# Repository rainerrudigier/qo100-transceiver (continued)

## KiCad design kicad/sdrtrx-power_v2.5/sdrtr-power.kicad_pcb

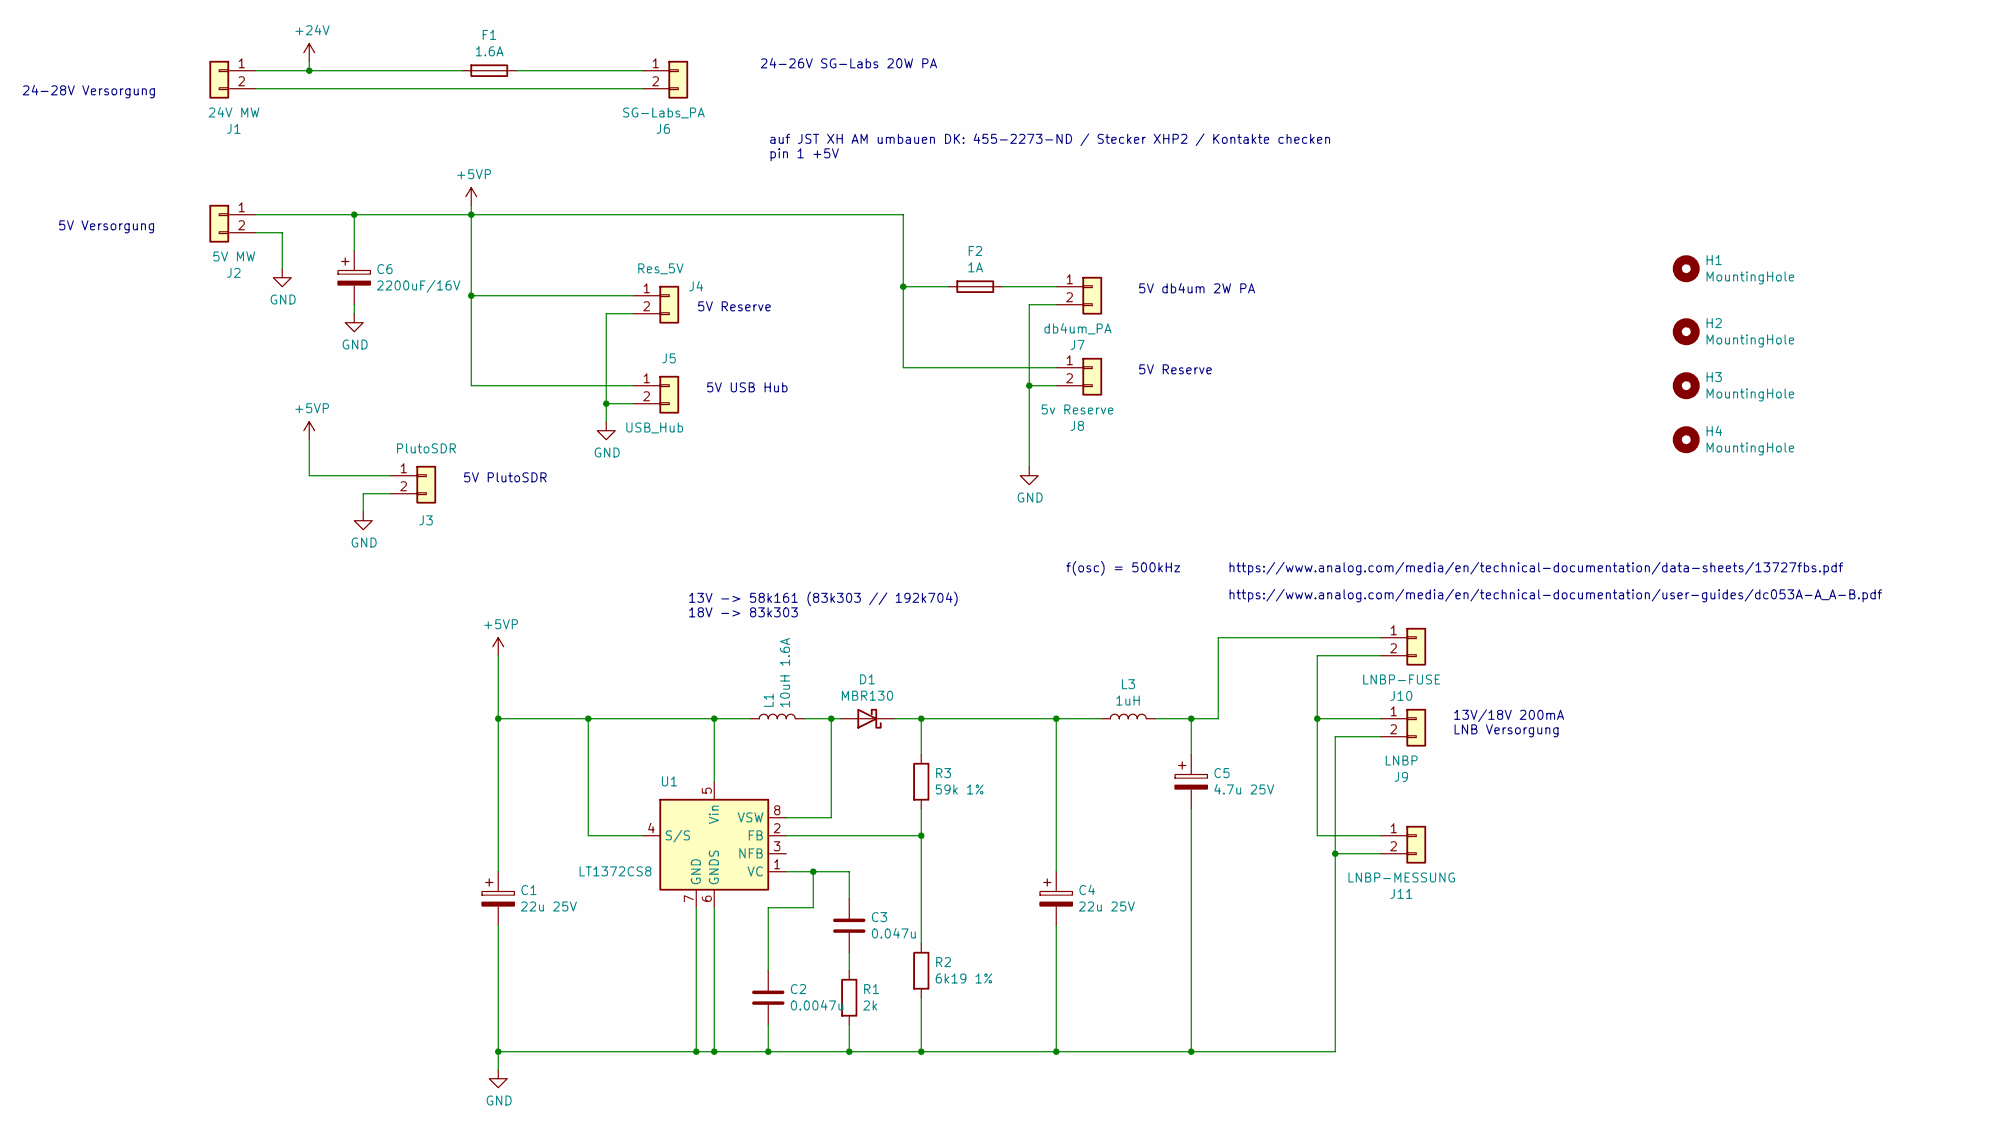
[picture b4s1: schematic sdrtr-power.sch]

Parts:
C1, C4: 22u 25V; CP_EIA-7343-30_AVX-N_Pad2.25x2.55mm_HandSolder; DigiKey 478-4106-1-ND
C2: 0.0047u; C_1206_3216Metric; DigiKey 478-10870-1-ND
C3: 0.047u; C_1206_3216Metric; DigiKey 478-3793-1-ND
C5: 4.7u 25V; CP_EIA-3528-15_AVX-H_Pad1.50x2.35mm_HandSolder; DigiKey 478-11105-1-ND
C6: 2200uF/16V; CP_Radial_D12.5mm_P5.00mm; Digikey 493-4884-1-ND
D1: MBR130; D_SOD-123; DigiKey MBR130T1GOSCT-ND
F1: 1.6A; Fuse_2920_7451Metric_Pad2.10x5.45mm_HandSolder; DigiKey F5965CT-ND
F2: 1A; Fuse_1210_3225Metric_Pad1.42x2.65mm_HandSolder; DigiKey F5964CT-ND
H1, H2, H3, H4: MountingHole; MountingHole_3.2mm_M3_Pad
J1: 24V MW; SolderWire-1sqmm_1x02_P5.4mm_D1.4mm_OD2.7mm
J2: 5V MW; SolderWire-1sqmm_1x02_P5.4mm_D1.4mm_OD2.7mm
J3: PlutoSDR; JST_XH_B2B-XH-AM_1x02_P2.50mm_Vertical; DigiKey 455-2273-ND
J4: Res_5V; JST_XH_B2B-XH-AM_1x02_P2.50mm_Vertical; DigiKey 455-2273-ND
J5: USB_Hub; JST_XH_B2B-XH-AM_1x02_P2.50mm_Vertical; DigiKey 455-2273-ND
J6: SG-Labs_PA; JST_XH_B2B-XH-AM_1x02_P2.50mm_Vertical; DigiKey 455-1704-ND
J7: db4um_PA; JST_XH_B2B-XH-AM_1x02_P2.50mm_Vertical; DigiKey 455-2273-ND
J8: 5v Reserve; JST_XH_B2B-XH-AM_1x02_P2.50mm_Vertical; DigiKey 455-2273-ND
J9: LNBP; Molex_PicoBlade_53047-0210_1x02_P1.25mm_Vertical; DigiKey WM1731-ND
J10: LNBP-FUSE; Molex_PicoBlade_53047-0210_1x02_P1.25mm_Vertical; DigiKey WM1731-ND
J11: LNBP-MESSUNG; Molex_PicoBlade_53047-0210_1x02_P1.25mm_Vertical; DigiKey WM1731-ND
L1: 10uH 1.6A; L_7.3x7.3_H3.5; DigiKey 308-2127-1-ND
L3: 1uH; L_1008_2520Metric; DigiKey 308-2608-1-ND
R1: 2k; R_0805_2012Metric; DigiKey 541-4134-1-ND
R2: 6k19 1%; R_0805_2012Metric; DigiKey 541-6.19KCCT-ND
R3: 59k 1%; R_0805_2012Metric; DigiKey 541-59.0KCCT-ND
U1: LT1372CS8; SOIC-8_3.9x4.9mm_P1.27mm; DigiKey LT1372CS8#TRPBFCT-ND

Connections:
+5VP: C1.1, C6.1, F2.2, J2.1, J3.1, J4.1, J5.1, J8.1, L1.1, U1.4 (S/S), U1.5 (Vin)
+24V: F1.2, J1.1
GND: C1.2, C2.2, C4.2, C5.2, C6.2, J2.2, J3.2, J4.2, J5.2, J7.2, J8.2, J9.2, J11.2, R1.2, R2.2, U1.6 (GNDS), U1.7 (GND)
unnamed: C2.1, C3.1, U1.1 (VC)
unnamed: C3.2, R1.1
unnamed: C4.1, D1.1 (K), L3.1, R3.1
unnamed: C5.1, J10.1, L3.2
unnamed: D1.2 (A), L1.2, U1.8 (VSW)
unnamed: F1.1, J6.1
unnamed: F2.1, J7.1
unnamed: J1.2, J6.2
unnamed: J9.1, J10.2, J11.1
unnamed: R2.1, R3.2, U1.2 (FB)

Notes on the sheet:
13V/18V 200mA LNB Versorgung
5V Versorgung
5V PlutoSDR
5V Reserve
5V USB Hub
5V db4um 2W PA
24-26V SG-Labs 20W PA
24-28V Versorgung
f(osc) = 500kHz
https://www.analog.com/media/en/technical-documentation/data-sheets/13727fbs.pdf
13V -> 58k161 (83k303 // 192k704) 18V -> 83k303
https://www.analog.com/media/en/technical-documentation/user-guides/dc053A-A_A-B.pdf
auf JST XH AM umbauen DK: 455-2273-ND / Stecker XHP2 / Kontakte checken pin 1 +5V

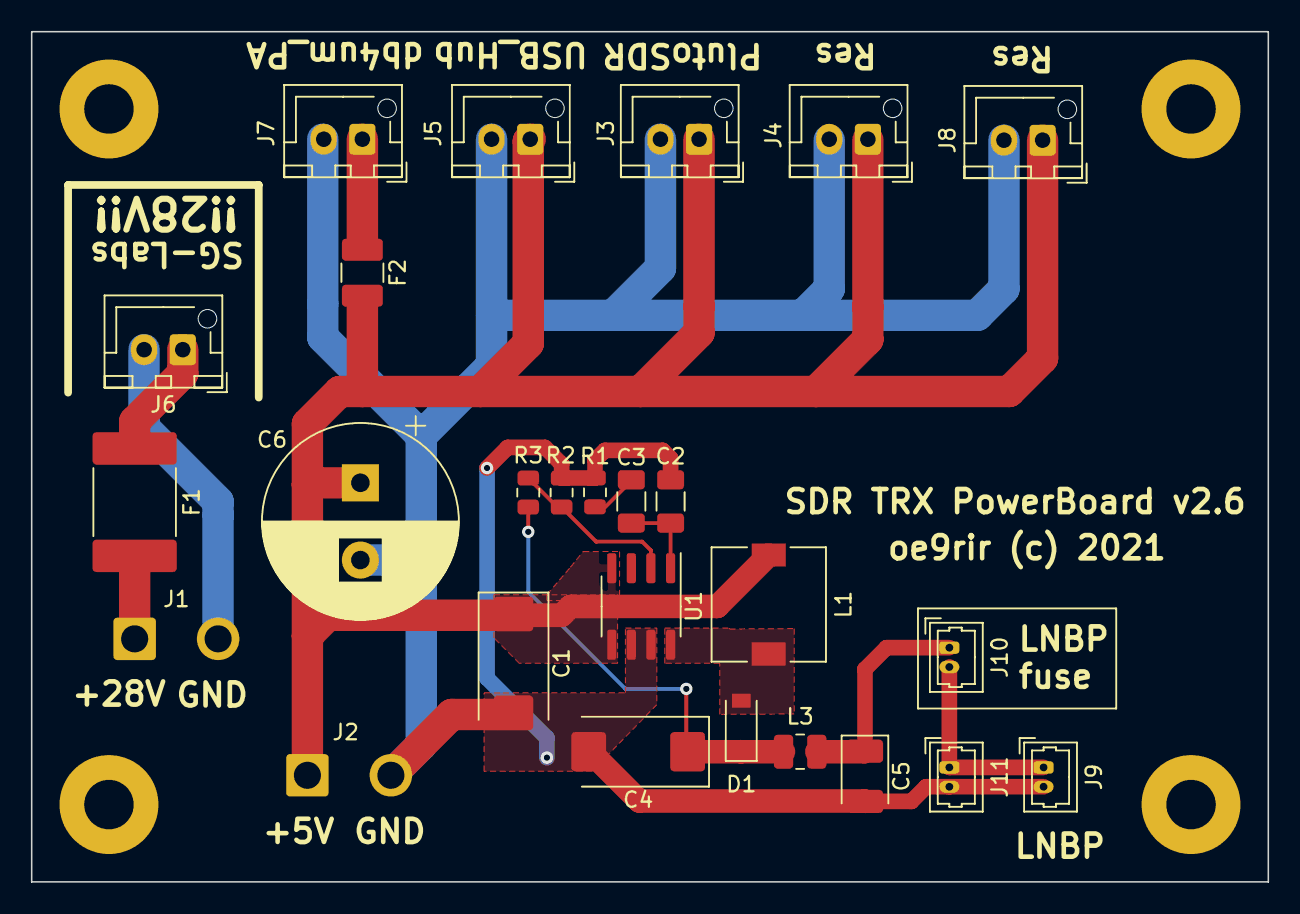
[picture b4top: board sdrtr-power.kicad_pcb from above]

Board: 2 copper layers, 80.0 x 55.0 mm, 30 parts (0 on the bottom side), 13 nets.

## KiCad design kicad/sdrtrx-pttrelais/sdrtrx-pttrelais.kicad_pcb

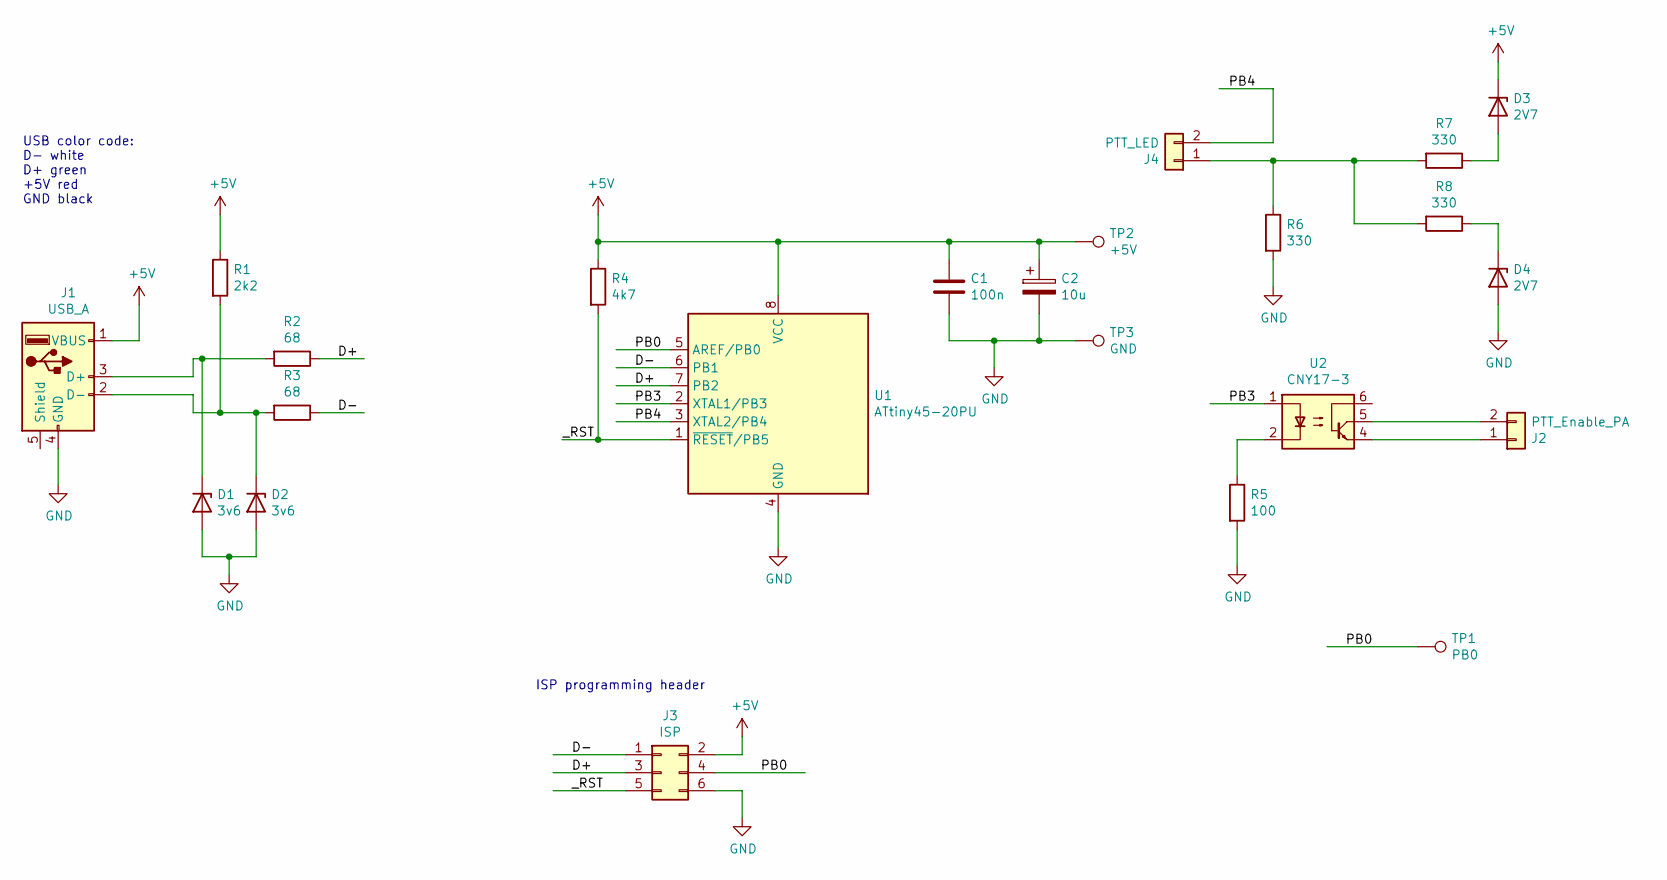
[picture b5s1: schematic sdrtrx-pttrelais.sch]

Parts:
C1: 100n; C_0805_2012Metric
C2: 10u; CP_Elec_4x5.8; Digikey 10-EEE-FN1A100RCT-ND
D1, D2: 3v6; D_SOD-123; Digikey MMSZ5227BT1GOSCT-ND
D3, D4: 2V7; D_SOD-123
J1: USB_A; USB_A_CNCTech_1001-011-01101_Horizontal; Digikey 1175-1008-ND
J2: PTT_Enable_PA; Molex_PicoBlade_53047-0210_1x02_P1.25mm_Vertical
J3: ISP; PinHeader_2x03_P1.27mm_Vertical
J4: PTT_LED; Molex_PicoBlade_53047-0210_1x02_P1.25mm_Vertical
R1: 2k2; R_0805_2012Metric
R2, R3: 68; R_0805_2012Metric
R4: 4k7; R_0805_2012Metric
R5: 100; R_0805_2012Metric
R6, R7, R8: 330; R_0805_2012Metric
TP1: PB0; TestPoint_Pad_D1.5mm
TP2: +5V; TestPoint_Pad_D1.5mm
TP3: GND; TestPoint_Pad_D1.5mm
U1: ATtiny45-20PU; SOIC-8_5.275x5.275mm_P1.27mm; Digikey ATTINY45-20SURCT-ND
U2: CNY17-3; CNY17_10x8.60mm_P2.54mm; Digikey CNY17-3X017TCT-ND

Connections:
+5V: C1.1, C2.1, D3.1 (K), J1.1 (VBUS), J3.2, R1.1, R4.1, TP2.1, U1.8 (VCC)
/D+: J3.3, R2.1, U1.7 (PB2)
/D-: J3.1, R3.1, U1.6 (PB1)
/PB0: J3.4, TP1.1, U1.5 (AREF/PB0)
/PB3: U1.2 (XTAL1/PB3), U2.1
/PB4: J4.2, U1.3 (XTAL2/PB4)
/_RST: J3.5, R4.2, U1.1 (~RESET~/PB5)
GND: C1.2, C2.2, D1.2 (A), D2.2 (A), D4.2 (A), J1.4 (GND), J3.6, R5.2, R6.2, TP3.1, U1.4 (GND)
unnamed: D1.1 (K), J1.3 (D+), R2.2
unnamed: D2.1 (K), J1.2 (D-), R1.2, R3.2
unnamed: D3.2 (A), R7.1
unnamed: D4.1 (K), R8.1
unnamed: J2.1, U2.4
unnamed: J2.2, U2.5
unnamed: J4.1, R6.1, R7.2, R8.2
unnamed: R5.1, U2.2

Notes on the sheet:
USB color code: D- white D+ green +5V red GND black
ISP programming header

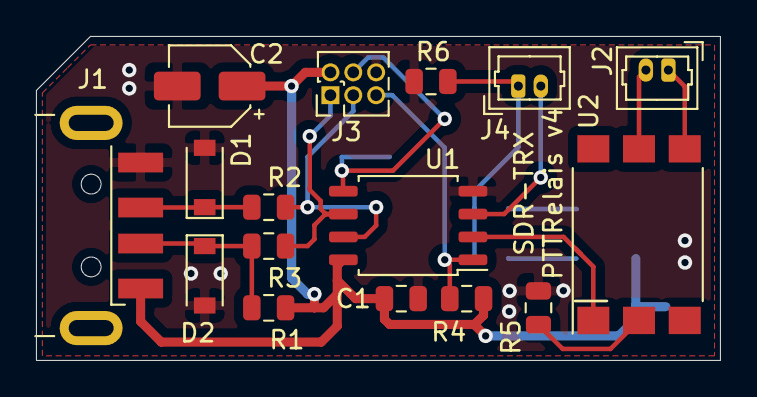
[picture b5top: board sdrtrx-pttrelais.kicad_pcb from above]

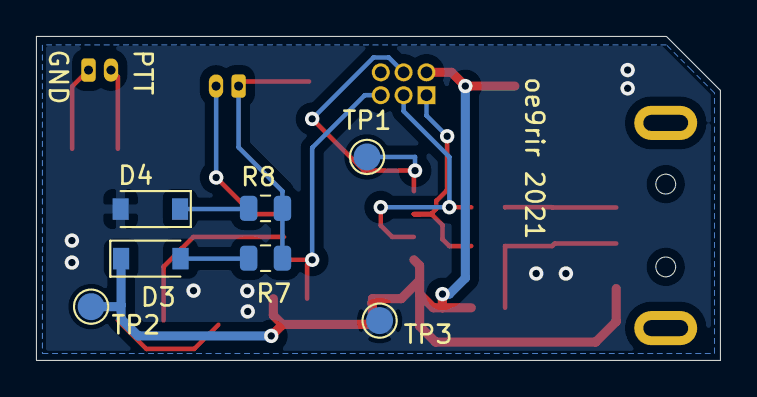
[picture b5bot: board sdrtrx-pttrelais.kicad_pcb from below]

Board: 2 copper layers, 38.0 x 18.0 mm, 23 parts (7 on the bottom side), 16 nets.

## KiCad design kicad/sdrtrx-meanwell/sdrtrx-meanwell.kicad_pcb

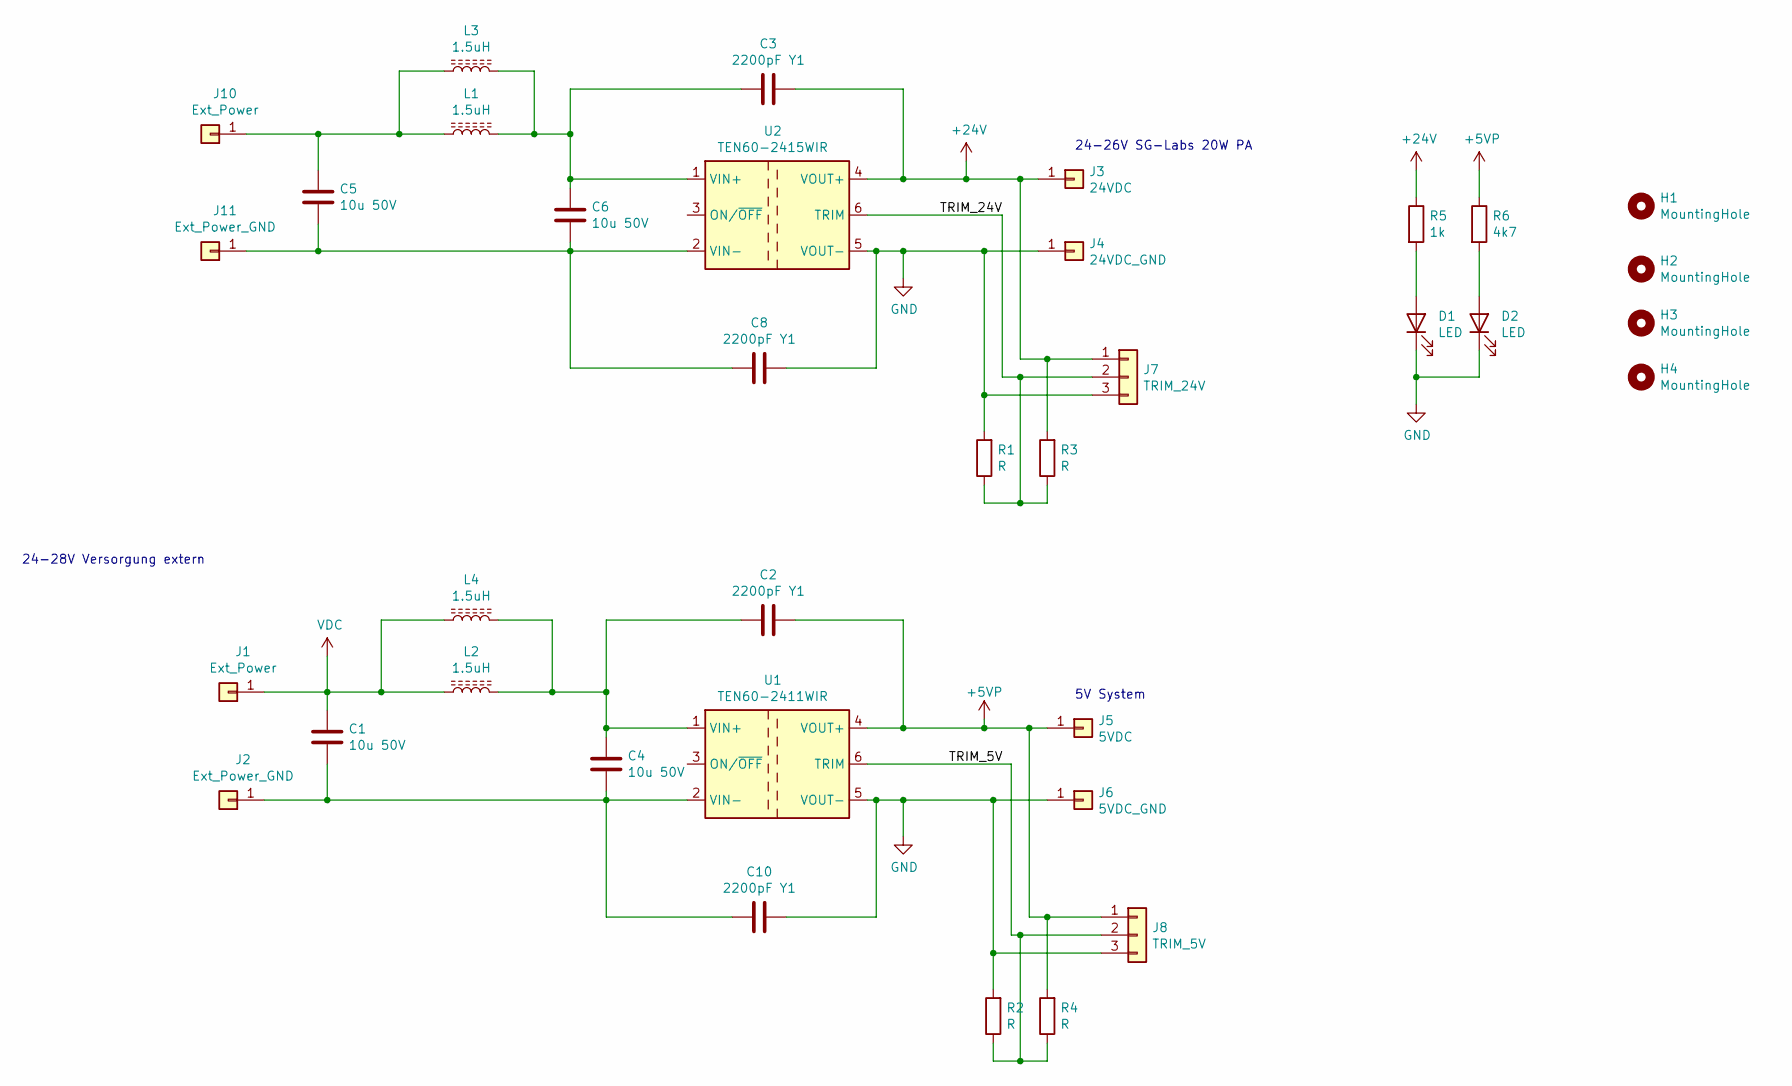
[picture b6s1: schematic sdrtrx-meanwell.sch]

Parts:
C1, C4, C5, C6: 10u 50V; C_1210_3225Metric_Pad1.42x2.65mm_HandSolder; DigiKey 399-C1210C106K5PAC7210CT-ND
C2, C3, C8, C10: 2200pF Y1; C_Disc_D11.0mm_W5.0mm_P10.00mm; DigiKey 490-16263-1-ND
D1, D2: LED; LED_0805_2012Metric
H1, H2, H3, H4: MountingHole; MountingHole_3.2mm_M3_Pad
J1, J10: Ext_Power; SolderWire-1sqmm_1x01_D1.4mm_OD2.7mm
J2, J11: Ext_Power_GND; SolderWire-1sqmm_1x01_D1.4mm_OD2.7mm
J3: 24VDC; SolderWire-1sqmm_1x01_D1.4mm_OD2.7mm
J4: 24VDC_GND; SolderWire-1sqmm_1x01_D1.4mm_OD2.7mm
J5: 5VDC; SolderWire-1sqmm_1x01_D1.4mm_OD2.7mm
J6: 5VDC_GND; SolderWire-1sqmm_1x01_D1.4mm_OD2.7mm
J7: TRIM_24V; Molex_PicoBlade_53398-0371_1x03-1MP_P1.25mm_Vertical; DigiKey WM7607CT-ND
J8: TRIM_5V; Molex_PicoBlade_53398-0371_1x03-1MP_P1.25mm_Vertical; DigiKey WM7607CT-ND
L1, L2: 1.5uH; L_Axial_L12.0mm_D5.0mm_P5.08mm_Vertical_Fastron_MISC
L3, L4: 1.5uH; L_Axial_L14.0mm_D4.0mm_P9.2mm_Horizontal_AML04A14-2R2M6R5-S1
R1, R2, R3, R4: R; R_0805_2012Metric_Pad1.15x1.40mm_HandSolder
R5: 1k; R_0805_2012Metric
R6: 4k7; R_0805_2012Metric
U1: TEN60-2411WIR; Converter_DCDC_TRACO_TEN60-xxxx_THT; DigiKey 1951-TEN60-2411WIR-ND
U2: TEN60-2415WIR; Converter_DCDC_TRACO_TEN60-xxxx_THT; DigiKey 1951-TEN60-2415WIR-ND

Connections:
+5VP: C2.2, J5.1, J8.1, R4.2, R6.1, U1.4 (VOUT+)
+24V: C3.1, J3.1, J7.1, R3.2, R5.1, U2.4 (VOUT+)
/TRIM_5V: J8.2, R2.1, R4.1, U1.6 (TRIM)
/TRIM_24V: J7.2, R1.1, R3.1, U2.6 (TRIM)
GND: C8.1, C10.1, D1.1 (K), D2.1 (K), J4.1, J6.1, J7.3, J8.3, R1.2, R2.2, U1.5 (VOUT-), U2.5 (VOUT-)
unnamed: C1.2, C4.2, C10.2, J2.1, U1.2 (VIN-)
unnamed: C2.1, C4.1, L2.2, L4.2, U1.1 (VIN+)
unnamed: C3.2, C6.1, L1.2, L3.2, U2.1 (VIN+)
unnamed: C5.1, J10.1, L1.1, L3.1
unnamed: C5.2, C6.2, C8.2, J11.1, U2.2 (VIN-)
unnamed: D1.2 (A), R5.2
unnamed: D2.2 (A), R6.2
VDC: C1.1, J1.1, L2.1, L4.1

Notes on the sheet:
5V System
24-26V SG-Labs 20W PA
24-28V Versorgung extern

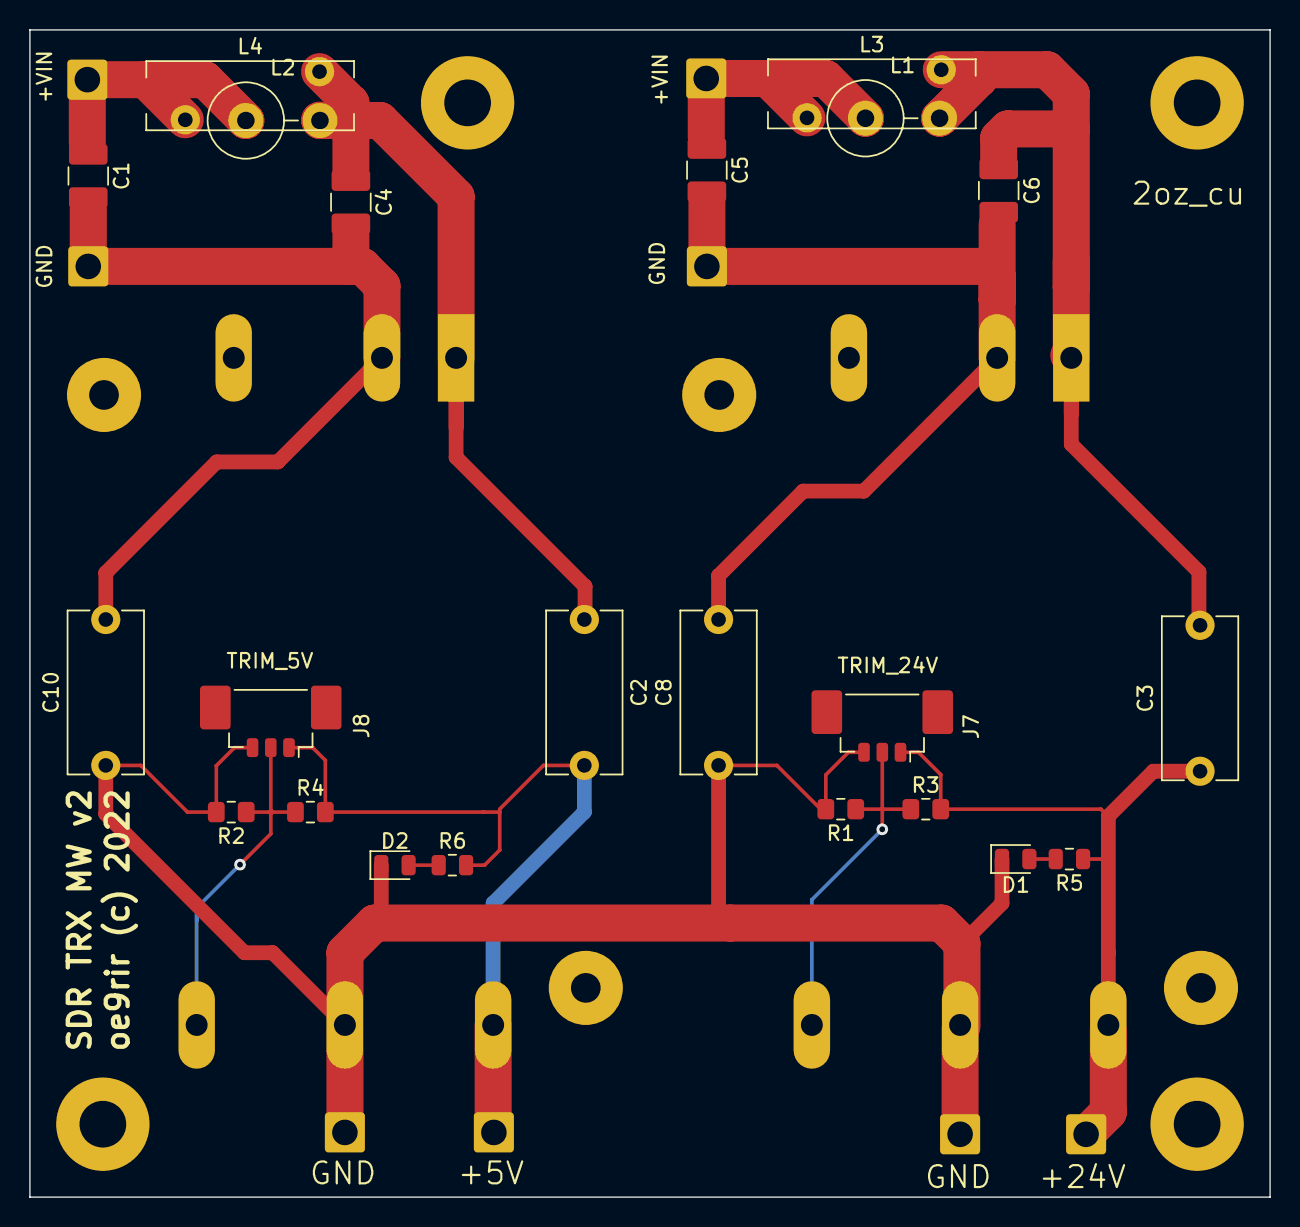
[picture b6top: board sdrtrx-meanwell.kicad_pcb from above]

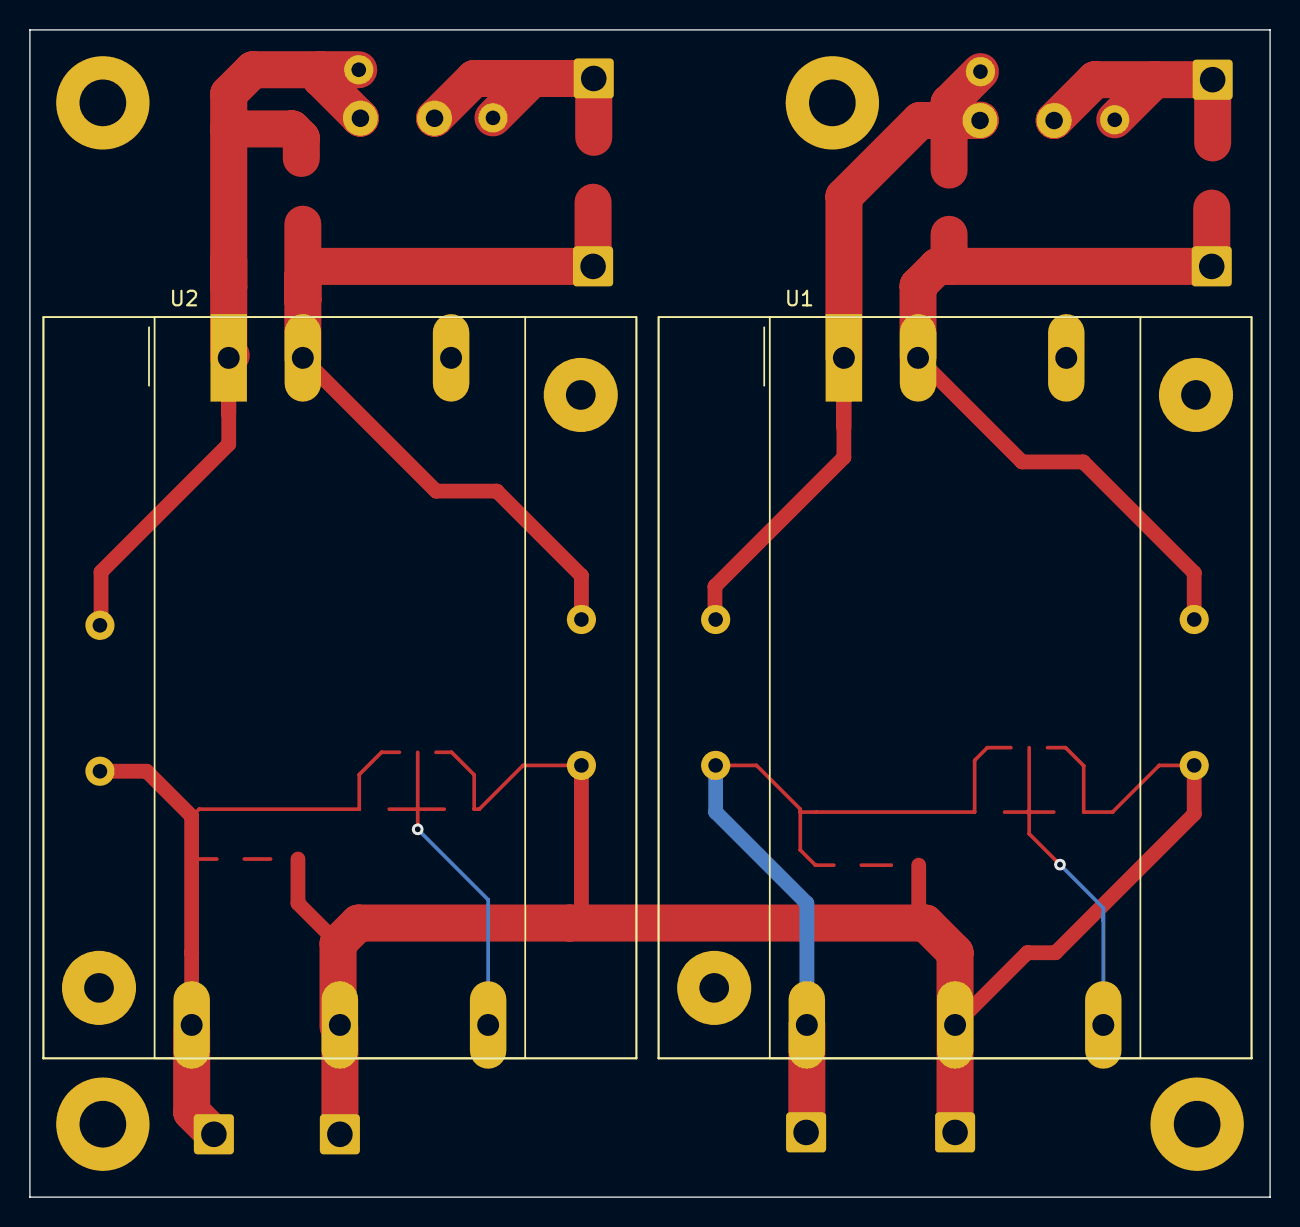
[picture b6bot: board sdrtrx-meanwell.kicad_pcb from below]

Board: 2 copper layers, 85.0 x 80.0 mm, 36 parts (2 on the bottom side), 13 nets.

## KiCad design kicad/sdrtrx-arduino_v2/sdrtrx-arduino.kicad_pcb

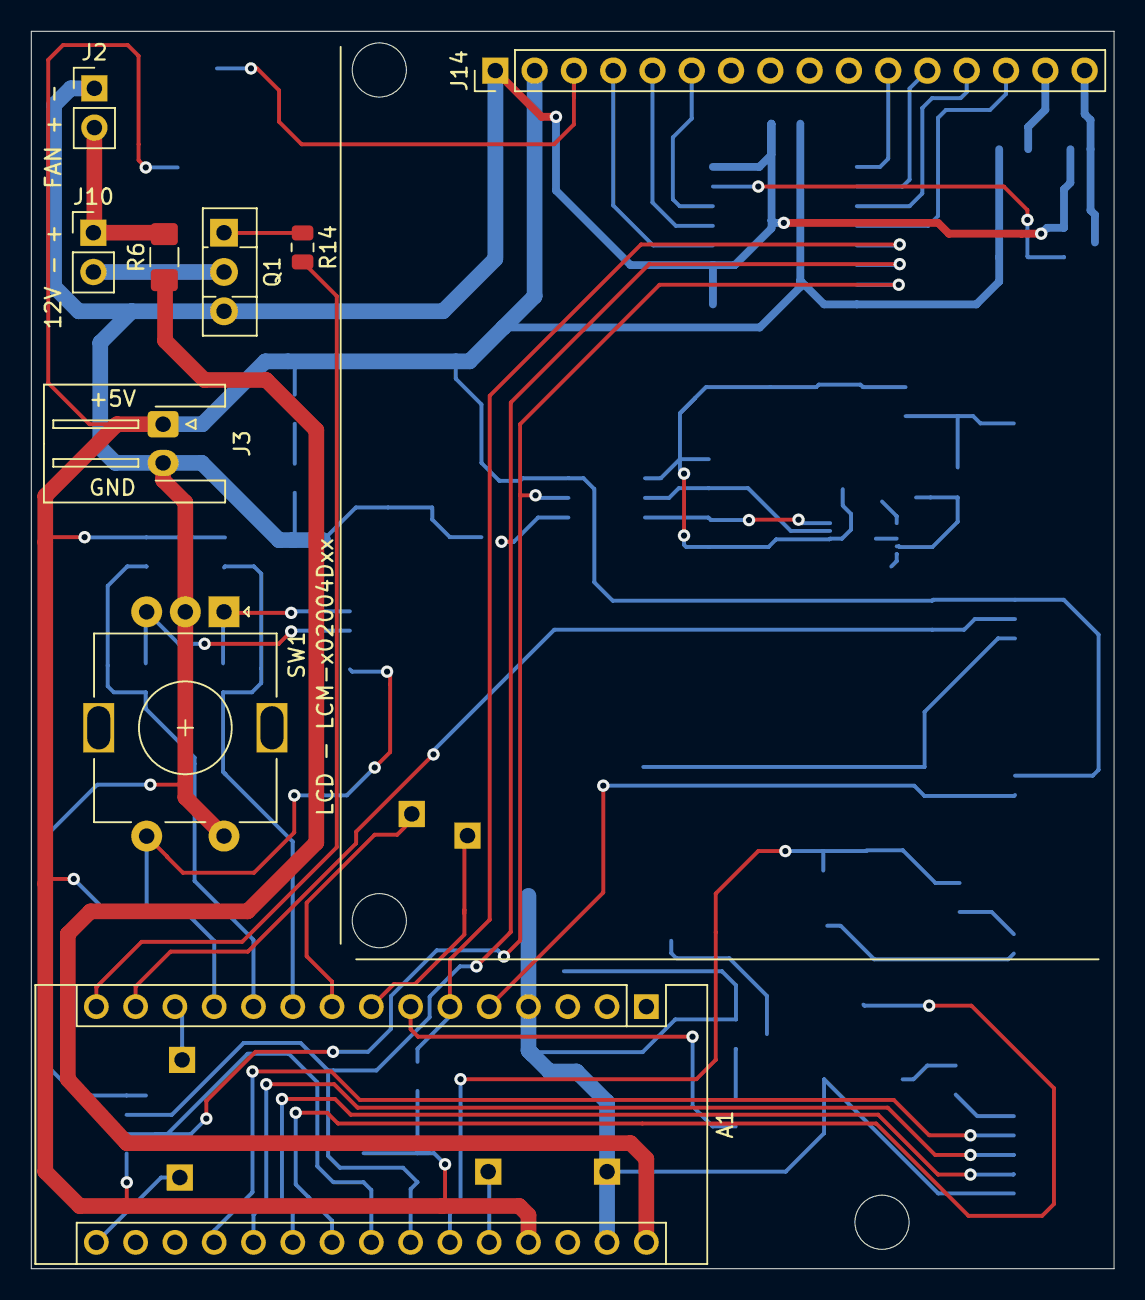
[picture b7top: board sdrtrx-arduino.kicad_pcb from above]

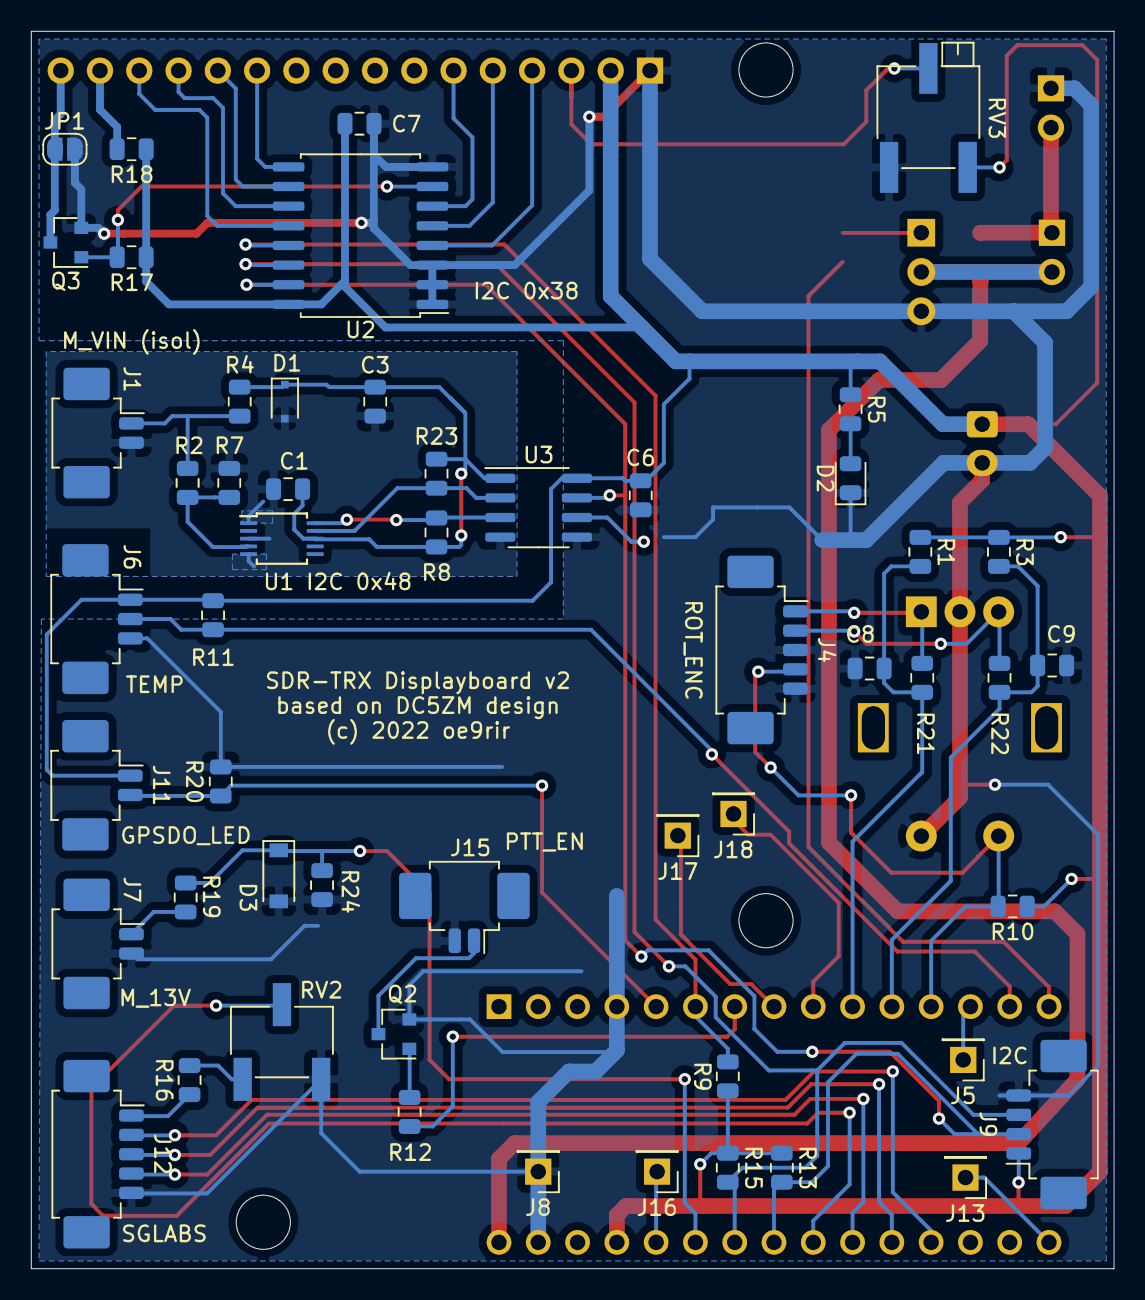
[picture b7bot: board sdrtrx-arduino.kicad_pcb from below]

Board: 2 copper layers, 70.0 x 80.0 mm, 65 parts (53 on the bottom side), 51 nets.

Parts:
A1: Arduino_Nano_v3.x; Arduino_Nano
C1, C3, C6, C7, C8, C9: 100n; C_0805_2012Metric
D1: MM3Z5V1; D_SOD-323F
D2: LED; LED_0805_2012Metric
D3: 3V3; D_SOD-123
H1, H2, H3: MountingHole; MountingHole_3.5mm
J1: TRX Input Power; Molex_PicoBlade_53261-0271_1x02-1MP_P1.25mm_Horizontal
J2: 12V_IN; PinHeader_1x02_P2.54mm_Vertical
J3: 5V Power Input; JST_XH_S2B-XH-A-1_1x02_P2.50mm_Horizontal
J4: Rot_SW; Molex_PicoBlade_53261-0571_1x05-1MP_P1.25mm_Horizontal
J5: D10; PinHeader_1x01_P2.54mm_Vertical
J6: Temp; Molex_PicoBlade_53261-0371_1x03-1MP_P1.25mm_Horizontal
J7: 13V_Messung; Molex_PicoBlade_53261-0271_1x02-1MP_P1.25mm_Horizontal
J8: GND; PinHeader_1x01_P2.54mm_Vertical
J9: I2C_external; Molex_PicoBlade_53261-0471_1x04-1MP_P1.25mm_Horizontal
J10: Fan; PinHeader_1x02_P2.54mm_Vertical
J11: GPSDO_LED; Molex_PicoBlade_53261-0271_1x02-1MP_P1.25mm_Horizontal
J12: SGL_Messung; Molex_PicoBlade_53261-0571_1x05-1MP_P1.25mm_Horizontal
J13: D13; PinHeader_1x01_P2.54mm_Vertical
J14: LCD_4x20 LCM-S02004DSF; PinHeader_1x16_P2.54mm_Vertical
J15: PTT_EN; Molex_PicoBlade_53261-0271_1x02-1MP_P1.25mm_Horizontal
J16: A7; PinHeader_1x01_P2.54mm_Vertical
J17: D5; PinHeader_1x01_P2.54mm_Vertical
J18: D6; PinHeader_1x01_P2.54mm_Vertical
JP1: BL_ON; SolderJumper-2_P1.3mm_Open_RoundedPad1.0x1.5mm
Q1: BD679; TO-126-3_Vertical
Q2, Q3: SBC817-40LT3G; SOT-23
R1, R3: 68k; R_0805_2012Metric
R2: 52k3; R_0805_2012Metric
R4, R5: 1k; R_0805_2012Metric
R6: 100; R_1206_3216Metric_Pad1.42x1.75mm_HandSolder
R7: 5k9; R_0805_2012Metric
R8, R9, R10, R13, R15, R20, R23: 10k; R_0805_2012Metric
R11, R16, R17, R19, R24: 4k7; R_0805_2012Metric
R12, R14: 470; R_0805_2012Metric
R18: 330; R_0805_2012Metric
R21, R22: 3k3; R_0805_2012Metric
RV2: 1k; Potentiometer_Bourns_3269W_Vertical
RV3: 10k; Potentiometer_Bourns_3269P_Horizontal
SW1: Rotary_Encoder_Switch; RotaryEncoder_CTS_MC290V-Switch_Vertical_H20mm
U1: ADS1113IDGS; TSSOP-10_3x3mm_P0.5mm
U2: PCF8574A; SOIC-16W_7.5x10.3mm_P1.27mm
U3: ISO1540; SOIC-8_3.9x4.9mm_P1.27mm

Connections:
+5V: A1.27, C6.1, C7.1, J3.1, J6.1, J9.1, J11.1, J14.2, R1.1, R3.1, R5.1, R9.1, R10.1, R11.1, R13.1, R15.1, R17.1, R18.1, RV3.1, U2.16, U3.8
+5VA: C1.1, C3.1, D1.1, R4.2, R8.1, R23.1, U1.8, U3.1
+12V: J2.2, J10.1, R6.2
/BL: Q3.1, R17.2, U2.7
/D4: J14.11, U2.9
/D5: J14.12, U2.10
/D6: J14.13, U2.11
/D7: J14.14, U2.12
/E: J14.6, U2.6
/FAN: A1.15, R14.2
/GPSDO_LED: A1.5, J11.2, R20.1
/M_13V: A1.25, D3.1, R19.2, R24.1
/PCF_INT: A1.6, R9.2, U2.13
/PTT_EN: A1.7, R12.2
/RS: J14.4, U2.4
/RW: J14.5, U2.5
/R_A: A1.10, C8.2, R1.2, R21.1
/R_A1: J4.1, R21.2, SW1.A
/R_B: A1.11, C9.1, R3.2, R22.2
/R_B1: J4.2, R22.1, SW1.B
/R_SW: A1.12, J4.4, R10.2, SW1.S1
/SCL: A1.24, J9.3, R15.2, U2.14, U3.6
/SDA: A1.23, J9.2, R13.2, U2.15, U3.7
/SGL_DRV: A1.21, J12.4
/SGL_FWD: A1.19, J12.2
/SGL_REV: A1.20, J12.3
/SGL_VIN: A1.22, RV2.2
/TEMP: A1.14, J6.2, R11.2
/VIN: A1.30, R6.1
GND: A1.4, A1.29, C6.2, C7.2, C8.1, C9.2, D2.1, D3.2, J2.1, J3.2, J4.3, J4.5, J6.3, J7.2, J8.1, J9.4, J12.5, J14.1, J15.2, JP1.2, Q1.3, Q2.2, Q3.2, R20.2, R24.2, RV2.3, RV3.3, SW1.C, SW1.S2, U2.1, U2.2, U2.3, U2.8, U3.5
GND1: C1.2, C3.2, D1.2, J1.2, R7.1, U1.1, U1.3, U1.5, U3.4
unnamed: A1.8, J17.1
unnamed: A1.9, J18.1
unnamed: A1.13, J5.1
unnamed: A1.16, J13.1
unnamed: A1.26, J16.1
unnamed: D2.2, R5.2
unnamed: J1.1, R2.1, R4.1
unnamed: J7.1, R19.1
unnamed: J10.2, Q1.2
unnamed: J12.1, R16.1
unnamed: J14.3, RV3.2
unnamed: J14.15, R18.2
unnamed: J14.16, JP1.1, Q3.3
unnamed: J15.1, Q2.3
unnamed: Q1.1, R14.1
unnamed: Q2.1, R12.1
unnamed: R2.2, R7.2, U1.4
unnamed: R8.2, U1.10, U3.3
unnamed: R16.2, RV2.1
unnamed: R23.2, U1.9, U3.2

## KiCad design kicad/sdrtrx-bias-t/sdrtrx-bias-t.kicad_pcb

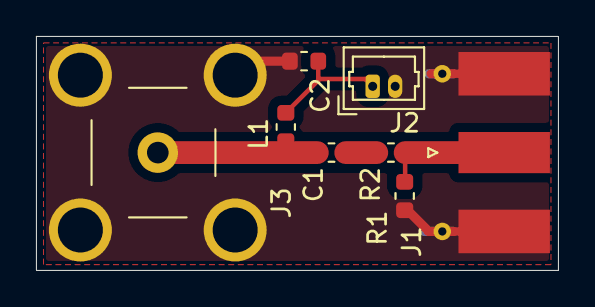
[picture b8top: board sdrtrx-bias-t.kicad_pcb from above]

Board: 2 copper layers, 29.0 x 13.0 mm, 8 parts (0 on the bottom side), 5 nets.

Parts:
C1, C2: 100p; C_0603_1608Metric
J1: SDR; SMA_Molex_73251-1153_EdgeMount_Horizontal
J2: 13V; Molex_PicoBlade_53047-0210_1x02_P1.25mm_Vertical
J3: LNB; F_Molex_73330-0030_Horizontal
L1: 39nH; L_0603_1608Metric
R1: 82; R_0603_1608Metric
R2: 47; R_0603_1608Metric

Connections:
GND: C2.1, J1.2, J2.2, J3.2, R1.2
unnamed: C1.1, J3.1, L1.1
unnamed: C1.2, R2.1
unnamed: C2.2, J2.1, L1.2
unnamed: J1.1, R1.1, R2.2

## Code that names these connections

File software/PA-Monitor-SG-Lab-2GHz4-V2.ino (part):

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
#define ONE_WIRE_BUS 11    //  Data wire is plugged into pin 12 on the Arduino 
#define TEMPERATURE_PRECISION 13
#define FAN_PIN 12
#define NO  0
#define YES 1

#define R_SW 9

#define GPSDO_LED_PIN 2


// ************************************************************** variables to be changed for calibration *********
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float    scc_drv = 1.0, scc_fwd = 1.0, scc_ref =  1.0 ;              // Shift_Calibration_Curve 0.93=7%> 1.07=7%< *
float    power_drv_min = 0.1;                                        // minimal power for calculation and display *
byte     power_fwd_min = 1, power_ref_min = 1 ,power_drv_max = 1;    // min. power for calc. and display          *
byte     temp_fan_on = 50, voltmeter_full_scale = 30;                // fan on at overtemperature, adjust att. R1 *
// ****************************************************************************************************************


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  lcd.init();                      // initialize the lcd 
  //lcd.init();
  sensors.begin();   // Start up the library 
  pinMode(FAN_PIN, OUTPUT);
  pinMode(R_SW, INPUT);
  digitalWrite(R_SW, true); // pull-up 

  pinMode(GPSDO_LED_PIN, INPUT);

  lcd.backlight();

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void loop(void) 
{ 

  int gpsdo_status = digitalRead(GPSDO_LED_PIN);

  if(gpsdo_status == HIGH)
  {
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  } 
  
  if(temperature >= temp_fan_on)
  {  digitalWrite(FAN_PIN, HIGH); fan_active = YES; }
  else
  {  digitalWrite(FAN_PIN, LOW) ; fan_active =  NO; }      
}
// -------------------------------------------------------------------------------------------------------------------

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
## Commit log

2022-11-01 inital version
